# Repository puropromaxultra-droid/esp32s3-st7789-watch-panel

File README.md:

# 桌面电子屏 · ESP32-S3 + 手表拆机 ST7789

> 一块 3.5 元的智能手表拆机屏，一颗 ESP32-S3，四层自制 PCB（34×50mm），
> 手写驱动、无第三方库：七页可交互界面、GIF 动画专辑、WiFi 天气时钟、手机推流放音乐。
>
> *A pocket-sized ESP32-S3 info panel driving a salvaged smartwatch ST7789 (240×240):
> hand-written driver, GIF album, weather clock and phone-streamed music. It also has
> a battery, a speaker and a custom 4-layer PCB.*
>
> **状态**：V5 板已打样、焊接、在用（2026-11）。代码、PCB、Gerber、BOM、嘉立创工程源文件都在本仓库。
>
> **⚠️ 补丁 1（2026-11-25）** 装机后发现两个**只能改板**的问题：A 键接在 IO0（BOOT strapping 脚），
> 焊错就每次上电进下载模式；老王屏的排线不居中且必须朝下，导致装壳后屏偏，下一版要把屏换到元件面、
> 电池和扬声器补到背面原屏区。两处都在「二、硬件」里单独写了 ⚠️ 小节，改板前先看。

---

## 一、能干什么

七页界面，短按 A 键翻页：

| 页 | 内容 |
|---|---|
| **GIF** | 240×240 动画，从外挂 flash 读，**支持多条专辑**（长按 A/B 切换，右上角显示 `2/5`） |
| **CLOCK** | 大号数字时间 + 日期 + 顶部天气（长按 B 立即刷新天气） |
| **FORECAST** | 三天卡片：日期、天气图标、最高/最低温、天气文字（长按重试） |
| **SUN** | 日出/日落时间 + 太阳轨迹弧与当前位置 + **月相**（名称、月龄、亮度%） |
| **MUSIC** | 音乐播放页：曲名（自动 1 行/2 行/跑马灯）、进度、**长按 A/B 调音量**（存 NVS） |
| **BAT** | 电池图标 + 百分比大字、电压、温度、充电状态（ADC + CHRG 脚） |
| **SYS** | WiFi 信号强度/IP、堆与 PSRAM、芯片温度、SPI 频率、运行时长 —— 排障用 |

**音乐**：手机浏览器打开 `http://<板子IP>/`，选本地音频文件，**由手机 JS 解码 + 重采样**
成 31250Hz/16bit/立体声，POST 到板子，写进外挂 flash 的 4MB 环形缓冲，再喂 I2S。

**开机**：Win98 风格四色旗 + 跑马灯 + 多声部开机音（可从按键跳过）。

**按键**：只有两个键。A = 翻页，B = 第二功能；**A+B 同按 700ms 回时钟**（随时逃生）。
长按按页面分派：MUSIC 音量、CLOCK 刷天气、GIF 切专辑、其余回时钟。

---

## 二、硬件

### 器件

| 件 | 型号 | 说明 |
|---|---|---|
| 屏 | ST7789 240×240 IPS | 手表拆机模块，`FPC-T1D3BP-129`，24P / 0.5mm |
| 主控 | **ESP32-S3-MINI-1-N8**（8MB，立创 C2913206） | LGA 底焊，板载天线（不是 1U） |
| 外挂 flash | **GD25Q128 16MB（U5）** | 存 GIF 专辑 + 音乐环形缓冲 + 音频 |
| 功放 | **MAX98357A（U4，QFN）** | I2S 直入 D 类，配 1609 8Ω 0.5W 喇叭 |
| LDO | XC6220B331MR | 500mA，WiFi 峰值不塌 |
| 防倒灌 | AO3401（Q2） | D=BAT S=VSYS G=VBUS |
| 电池 | 602535 软包 500mAh（带保护板） | TP4056-42 **ESOP-8** 充电 |
| PCB | **34 × 50 mm，4 层 1.6mm** | 嘉立创 ¥50/5 片 |

### 引脚（V5 一体板，和外接面包板的编号不同！）

| 功能 | GPIO |
|---|---|
| LCD SCK / MOSI / CS / DC / RST / BL | **12 / 11 / 10 / 9 / 14 / 13** |
| I2S BCLK / LRC / DIN | **15 / 16 / 17** |
| 电池 ADC | 1 |
| 充电状态 CHRG | 2 |
| 按键 A / B | **0（飞线 J6.1）/ 5** |
| U5 flash（16MB，HSPI） | CS 21 / SCK 38 / MOSI 39 / MISO 40 |

#### ⚠️ A 键（补丁 1：这一版踩的坑，务必先读）

**为什么会长成这样**——四步错下来的，每一步都合理，合起来就废了：

1. **原设计**：A 键走 `SW1 → BTN_A 网络 → U1 的 pad 8`，也就是 **IO4**。
2. **实板翻车**：U1 是 LGA 底焊，IO4 那个焊盘虚焊，按键按下去信号根本出不了模组——
   表现为「键完全没反应」，不是接触不良那种时灵时不灵。底焊脚没法补焊，只能飞线绕开。
3. **飞线选错脚**：板上的 **J6 是 1×02 排针，pad1 = IO0、pad2 = GND**，看着天生就是个按键口，
   就把 A 键改到 IO0 上——**当时只确认了"这两根针空着"，没确认 IO0 上电时是什么状态**。
4. **接线再错一次**：SW1 是 4 脚轻触开关，**pad1/pad2 在板上直接接 GND，只有 pad3/pad4 是 BTN_A 信号**。
   飞线落在 pad1/pad2 上，等于把 IO0 焊死在 0V。

> 这些都能在工程文件里自己核（`hardware/LCD-board-V5_2026-11-08.epro2`）：
> `SW1: pad1/2→GND, pad3/4→BTN_A`；`U1: pad4→IO0, pad8→BTN_A(=IO4), pad9→IO5(=BTN_B)`；
> `J6: pad1→IO0, pad2→GND`；`J5: pad1→BAT, pad2→GND`（电池口，别搞混）。

**于是**：IO0 被拉低，芯片在上电那一刻判定"要烧录"，直接进 ROM 下载模式——屏黑、程序不跑，
但串口照样能烧录成功。这就是最坑的地方：**看起来像程序坏了，其实是脚被按住不放**。

问题的根在于 **IO0 不是普通 GPIO，它是 ESP32-S3 的 BOOT strapping 脚**：

| 现象 | 原因 |
|---|---|
| 插电屏全黑、程序不跑，但串口能烧录 | IO0 在上电/复位瞬间是**低**，进了 ROM 下载模式 |
| 松手也进不去系统，必须先拔线再插 | SW1 有一端误焊到 GND 侧，IO0 被**常拉低** |
| 烧录成功但按 RST 不重启 | 同上，复位时 IO0 仍为低 |

补焊/返修时只有一条正确接法：

- **飞线两端 = J6.1（IO0）↔ SW1 的 pad3 或 pad4**。这两个脚才是 BTN_A 信号脚；
  SW1 的 pad1/pad2 板上已经连死 GND，**不要碰**，碰了就是 IO0 常接地；
- ★ 判定方法：万用表蜂鸣档量 SW1 相邻两脚——**响的那一对是 GND**，另一对才是信号；
- 装壳后**上电、按 RST 时不要按着 A**，松手再上电（按下 = IO0 变低，同样进下载模式）；
- 验收：量 **IO0 ↔ GND**，松手必须回到 **≥3.0V**（芯片内部上拉），按下去才接近 0V。
  松手还是 0V 就是焊错或搭锡，别急着怀疑程序。

现场怎么验：串口发 **`b`** 打实时电平 —— `[btn] A=H B=H (H=松开 L=按下)`，
按一下 A 应变 `L`，松手立刻回 `H`。串口灯一直刷 `L` = IO0 被短路到地，先查焊点。
再用 **`e`** 核对计数（先发 `E` 清零，按 10 下，`down A` 应该是 10）；
`down` 偏少是电信号没进来（飞线/触点），`down` 对但 `short` 少是被双键同按吞了。

> **下一版必须把 A 键挪到非 strapping 的普通 GPIO**，否则这个坑会跟着外壳一起交付。
> B 键（IO5）没有这个问题。

#### ⚠️ 结构装配：屏排线不居中，而且只能朝下（补丁 1）

老王这块拆机屏（`FPC-T1D3BP-129`）有两个物理事实，直接否掉了"屏体居中"这个最直觉的排布方式：

1. **FPC 排线不在屏体正中**，出线口偏向一侧。屏体按外框居中装上去，**可视区就是偏的**，
   外壳的衬边一边宽一边窄，肉眼很明显。
2. **排线只能朝下出**。这块屏的 FPC 是单面翻折，朝上或朝侧都会折到屏体背面、塞不进后腔。

所以定位基准只能是 **「可视区中心」+「FPC 向下」**，不能拿屏体外框当基准。
偏置量逐块量，别套用别人的数值（同一批拆机屏都不完全一致）。

**V5 的排布是错的，改法是屏换面：**

| | V5（原设计） | 补丁 1（正确排布） |
|---|---|---|
| 屏 | B 面（背面），y≈10~39.5 | **F 面（元件面）** |
| 电池 + 扬声器 | 分散在 B 面剩余区域 | **占用 B 面原来屏占的那块** |
| 排线方向 | 朝上（J1 在板顶 Y 11.05，屏体压在排线下方） | **朝下**，自然出板边 |

屏换到元件面后，背面整块空出来正好给电池（602535）和喇叭，不用再抢角落。
**J1（FPC 座）必须跟着屏走**：V5 里它在 **X 17.00 / Y 11.05**（贴板顶，通道 x 11.2~22.8、y 8~15.5），
排线改朝下以后这个位置一定得挪，别照着 V5 的坐标抄。

**装配顺序别搞反，反了一定返工：**

1. 先定 FPC 出线方向 = **向下**；
2. 再按**可视区**居中定屏位（不是屏体外框）；
3. 最后才排电池和扬声器 —— 它们的形状受限最小，天然是让位的一方。

> 嘉立创 EDA 工程源文件：`hardware/LCD-board-V5_2026-11-08.epro2`（2026-11-08 定稿，含 PCB + 原理图）。
> 上面这套改法还没落到工程里，是**下一版要改的**；那份文件是改之前的状态，别直接打样。

### 最小验证接线（面包板 / FPC 转接板）

```
转接板排针                  →  ESP32-S3
1  (LED+)                   →  3V3
2  (LED-)                   →  GND
4  (VCC)                    →  3V3
5  (IOVCC)                  →  3V3
11 (RD)                     →  3V3      ← 串口模式选择，SPI 模式下也要拉高
23 (逻辑地)                 →  GND      ← ★ 必须接，只接 LED- 不够
9  (SCK)                    →  IO4
12 (SDA/MOSI)               →  IO5
8  (CS)                     →  IO6
10 (DC)                     →  IO7
7  (RST)                    →  IO8
6  (IM)                     →  IO9      ← ★ 必须为高电平，见下
```

> **这张表是「镜像」的。** 转接板座子的 pin1 方向与屏排线丝印相反，硬插会把
> 3V3 撞到屏的 GND 触点上（会发烫）。本项目没翻排线，而是把杜邦线按 `排针 n ↔ 屏触点 25-n`
> 映射改插到镜像位置。你若能自由选择方向，优先按物理正序插，别用这张镜像表。

---

## 三、踩过的坑（这个项目 90% 的时间都在这）

### 1. IM 脚必须为高电平 — 否则背光亮、屏全黑

ST7789 的 `IM0/IM1/IM2` 决定接口模式。**IM 为低时不是 4 线 SPI 模式，初始化指令完全不生效**，
症状是：背光正常亮、屏幕纯黑。

这条坑了整整一天，期间误判成「WiFi 库干扰」「固件太大」「杜邦线撑不住 20 MHz」，全是假象。
结论来自原厂开源工程 [`BA4IHS/GD32E230-LaoWang`](https://github.com/BA4IHS/GD32E230-LaoWang)，
其 `TFT_LCD_Init()` 第一行就是 `TFT_LCD_IM12(1);`。

```cpp
digitalWrite(PIN_IM, HIGH);   // 不能省，也不能拉低
```

### 2. 逐字节 `SPI.transfer()` 是性能灾难

`SPI.transfer(uint8_t)` 每次都要等上一字节发完，实测 **1.5–2 µs/字节**。
一帧 115200 字节 → **约 200ms，只有 5fps**。而且**提高 SPI 时钟完全没用**，
瓶颈在 CPU 调用开销，不在时钟。

换成 `SPI.writeBytes()` 批量（每批 16 行 = 7680 字节），整帧期间 CS 保持低、
`0x2C` 只发一次（窗口在全屏初始化时设好），立刻变成 **约 35ms/帧**。

| 方案 | 单帧 | 帧率 |
|---|---|---|
| 10 MHz + 逐字节 `transfer()` | ~200 ms | ~5 fps |
| 26 MHz + `writeBytes()` 批量 | ~35 ms | 跑满 GIF 的 16.7 fps |
| 80 MHz + 批量 + 双核流水线 | **15.1 ms** | 60+ fps（推屏上限） |

### 3. 逻辑地必须单独接

只接 `LED-` 时背光能亮，但屏的逻辑地悬空 → 全黑。转接板的 1/2/22 都是 GND，
至少要保证逻辑地有回路。

### 4. FPC 座插反 = 3V3 被拉塌，症状伪装成「屏黑 + USB 反复枚举」

反过来插会把 3V3 短到 GND。看上去像固件坏了、像 USB 线不好、像模组烧了，
**实际是座子方向错了**。先摸屏排线附近烫不烫，再查软件。

### 5. QFN 的 EP 锡厚会把芯片顶起来，十几脚一起虚焊

MAX98357A（U4）底部的散热焊盘上锡太多，芯片被顶高 0.1mm，**16 个脚全部没接触到焊盘**。
现象：一切正常，就是没声音。

修法：涂助焊剂，风枪 280~300°C 从底部吹 40~60s 让它自己回流坐下。
**没声先查 EP，不要先怀疑 I2S 时序。**

### 6. 采样率不是随便填的：MCLK/fs 必须是 128 / 256 / 384 / 512

一开始设 40000Hz，听到的是**沙沙声**——因为 PLL 拆不出整数分频。
31250Hz 能整除（MCLK 8MHz），于是本项目所有音频都锁在 31250Hz。
★ 别为了「好听」改成 44100，除非整条时钟链重新算。

### 7. flash 擦除会拖死播放，以及「对称去抖」是个陷阱

- 64KB 块擦是**原子操作 150ms**，而 8KB 读缓冲只够 131ms → 必须用 32KB（94ms），
  并且**只在刚 refill 完那一刻擦**，交给独立任务做。实测播放速率才从 51200 爬到 62958 B/s。
- 按键用对称去抖（`millis()-tRaw > 20`）**永远等不到**：氧化触点一次按动是 1~3ms 的脉冲串，
  每个断点都在刷新计时器。改成**计数式**：1ms 采样、连续 2 次 LOW 判按下、松手等 16ms。

---

## 四、目录

| 路径 | 说明 |
|---|---|
| **`weather_clock/`** | ★ **主程序**。多文件拆分：`weather_clock.ino`（UI/页面/按键）+ `tft.h`（驱动）+ `gif_store.h`（GIF 专辑）+ `u5flash.h`（16MB flash）+ `spk.h`（音效合成）+ `player.h`/`webstream.h`（推流播放）+ `www.h`（手机端网页）+ `audio.h`（WAV 播放） |
| **`hardware/`** | ★ **V5 四层 PCB**：KiCad 工程、Gerber、BOM、采购清单、`EDA-画板指南.md`（314KB 实战记录，§1~§40）。**`LCD-board-V5_2026-11-08.epro2`** = 嘉立创 EDA 工程源文件（PCB + 原理图，补丁 1 之前的状态） |
| `tools/album.py` | **GIF 专辑管理**：`list / add / rm / mv / order / migrate`，走串口 |
| `tools/screenshot.py` | **串口截图**：发 `Z` 导当前帧、`z` 重画 logo 后导出，存 PNG。调 UI 不用靠眼睛 |
| `tools/转换GIF.bat` | 把 GIF 拖上去 = 转码 + 上传 + 写索引（一条龙） |
| `tools/gif2bin.py` | GIF → 板端格式（缩放/抽帧/降色/RLE），单帧超限自动降色 |
| `tools/btn_diag.py` `vol_test.py` | 按键计数、音量台阶的自动化验证 |
| `lcd_fast/` `lcd_player/` | 早期驱动版本（可直接对比 `transfer()` 与 `writeBytes()` 的差异） |
| `bare_lcd_test/` | 最小验证：初始化 + 纯色 + 彩条，用来确认接线 |
| `gif_player*/` `*_probe/` `*_test/` | 排查过程留下的探针程序，保留作记录 |

---

## 五、编译与烧录

1. Arduino IDE + **esp32 core 4.0.x**
2. **必须有 `weather_clock/secrets.h`**（已 gitignore）：
   ```cpp
   #define WIFI_SSID "your-ssid"
   #define WIFI_PASS "your-pass"
   ```
   从 `secrets.h.example` 复制改名。
3. 板子选 **ESP32-S3 Dev Module**，下面两项**必须改**，否则屏黑或刷不进去：
   - **USB CDC On Boot: `Enabled`** ← 不开就看不到串口输出
   - **Partition Scheme: `Huge APP (3MB No OTA/1MB SPIFFS)`** ← 否则固件装不下
4. 串口 115200。正常启动会依次打印 WiFi、NTP、天气、U5、专辑索引、缓冲分配。

### 串口命令

| 键 | 作用 |
|---|---|
| `n` / `p` | 下一页 / 上一页 |
| `l` / `L` | 注入「长按 A / 长按 B」 |
| `H` | 注入「A+B 同按」 |
| `P` | 打印当前页 / 音量 / 推流状态 |
| `h` | 推流统计（`rd` 必须 ≈ **62500 B/s**） |
| `y` | 只灌 I2S 静音块，测纯时钟速率（应 ≈ 31499Hz） |
| `Z` / `z` | 导出当前帧 / 重画 logo 后导出（配合 `screenshot.py`） |
| `V` / `I` | 读 / 写专辑索引 |
| `e` / `E` | 按键计数 / 清零 |
| `U` / `A` | 上传 GIF / 音频 |

---

## 六、换 GIF、加音乐

**GIF**：把 `.gif` 拖到 `tools\转换GIF.bat` 上 → 自动转码 + 上传 + 写索引，屏上长按 A/B 切换。
或用命令行：

```bat
python tools\album.py add my.gif        :: 追加一条
python tools\album.py list              :: 看现有条目与占用
python tools\album.py rm 1              :: 删第 2 条（只改索引，数据等覆盖）
python tools\album.py mv 1 0            :: 调顺序
```

**音乐**：手机连同一 WiFi，浏览器开 `http://<屏上 SYS 页显示的 IP>/`，选文件即可播放。
网页里是 JS 解码 + 本地重采样到 31250Hz，**浏览器不给用的采样率会自动兜底**。

---

## 七、已知问题

- **A 键焊在 IO0 上（硬件缺陷）**：IO0 是 BOOT strapping 脚，IO0 被拉低时上电即进下载模式，
  软件无法规避。详见「二、硬件」的 A 键小节，下一版必须换脚。
- **屏装壳后不居中（结构缺陷）**：屏排线不在屏体正中，且只能朝下，V5 的屏位没考虑这一点。
  下一版屏换到元件面（F 面），电池和扬声器补到背面原屏区，详见「二、硬件」的装配小节。
- **天气接口只能走明文 HTTP**：`api.open-meteo.com` 的 ECDSA 证书会让 mbedTLS 握手失败，
  所以用了 HTTP/80 + 自计时 DNS。
- GIF 播放推到 8~17fps 取决于帧体积；单帧 >41KB 时转码脚本会自动降色。
- 外挂 flash 的 16MB 分了区：`0~2MB` 专辑、`2~6MB` 音乐环形、`8~16MB` 音频，
  其余留给将来。
- USB 供电不足时（满音量 + 满亮 + 推流），个别机器会欠压复位。

---

## 八、还有第二版

第二版是**重新设计的便携播放器**（TF 卡本地解码、侧装双喇叭、3.5mm 耳机、50×40 板），
不在本仓库，也不建议从本仓库改——音频架构完全不同。设计稿在另一个项目里，尚未开工。

---

## 致谢

- [`BA4IHS/GD32E230-LaoWang`](https://github.com/BA4IHS/GD32E230-LaoWang) — 原厂模块开源固件，
  IM 电平与完整初始化序列的结论出自这里
- ST7789 datasheet（写周期 16ns，SPI 上限约 62.5MHz）
- 立创 EDA / 嘉立创（打样）

## License

MIT，见 [LICENSE](LICENSE)。

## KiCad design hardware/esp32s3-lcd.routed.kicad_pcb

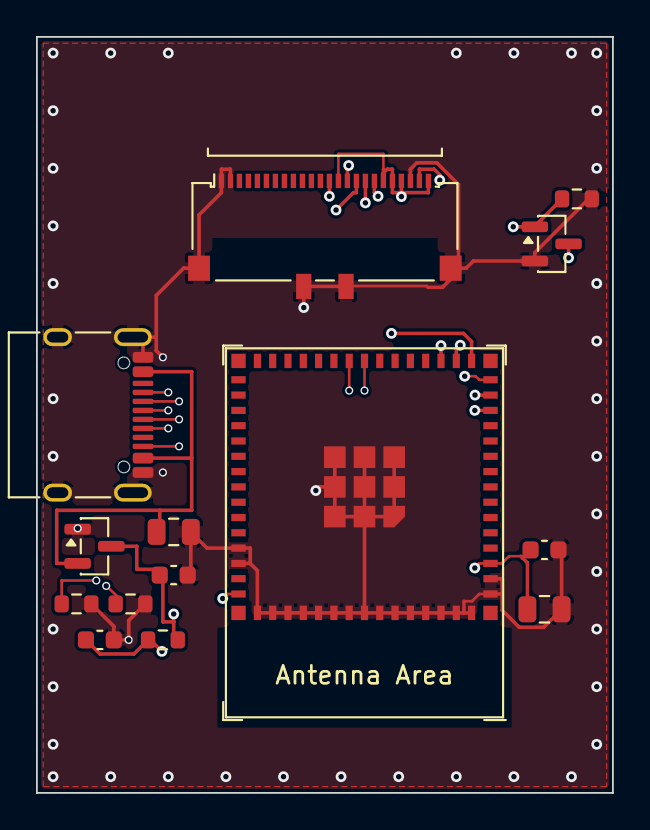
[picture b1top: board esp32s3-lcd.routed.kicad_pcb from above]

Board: 4 copper layers, 32.0 x 42.0 mm, 14 parts (0 on the bottom side), 15 nets.

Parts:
C1, C4: 10uF; C_0805_2012Metric
C2: 1uF; C_0603_1608Metric
C3, C5: 100nF; C_0603_1608Metric
J1: FPC 24P 0.5mm; Molex_502244-2430_1x24-1MP_P0.5mm_Horizontal
J2: USB-C 16P 单排; USB_C_Receptacle_XKB_U262-16XN-4BVC11
Q1: AO3400A; SOT-23
R1, R2: 5.1k; R_0603_1608Metric
R3: 10k; R_0603_1608Metric
R4: 100k; R_0603_1608Metric
U1: ESP32-S3-MINI-1-N8; ESP32-S3-MINI-1
U2: XC6206P332; SOT-23

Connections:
+3V3: C2.1, C3.1, C4.1, J1.14, J1.19, J1.20, J1.21, J1.24, R3.2, U1.3, U2.3
CC1: J2.A5, R1.1
CC2: J2.B5, R2.1
EN: C5.1, R3.1, U1.45
GND: C1.2, C2.2, C3.2, C4.2, C5.2, J1.1, J1.2, J1.22, J1.MP, J2.A1, J2.A12, J2.B1, J2.B12, J2.SH, Q1.2, R1.2, R2.2, R4.2, U1.1, U1.2, U1.42, U1.43, U1.46, U1.47, U1.48, U1.49, U1.50, U1.51, U1.52, U1.53, U1.54, U1.55, U1.56, U1.57, U1.58, U1.59, U1.60, U1.61, U2.1
LCD_BL: Q1.1, R4.1, U1.17
LCD_CS: J1.17, U1.14
LCD_DC: J1.15, U1.13
LCD_MOSI: J1.13, U1.15
LCD_RST: J1.18, U1.18
LCD_SCK: J1.16, U1.16
LED_K: J1.23, Q1.3
USB_DM: J2.A7, J2.B7, U1.23
USB_DP: J2.A6, J2.B6, U1.24
VBUS: C1.1, J2.A4, J2.A9, J2.B4, J2.B9, U2.2

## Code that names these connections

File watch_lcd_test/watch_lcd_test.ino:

/*
 * 手表拆机屏点亮测试（ESP32-S3 N16R8 + LovyanGFX）
 * ------------------------------------------------
 * 依赖：Arduino IDE 库管理器搜索 "LovyanGFX" 安装
 * 板型：ESP32S3 Dev Module（Flash 16MB，PSRAM 关闭即可，本例用不到）
 *
 * 接线（屏板 8 焊盘，顺序以板子丝印为准）：
 *   3V3  -> VCC（先试 3.3V；背光不亮再改接 5V）
 *   IO4  -> SCL   IO5  -> SDA
 *   IO6  -> DC    IO7  -> RES
 *   IO15 -> CS    IO16 -> BLK
 *   GND  -> GND
 *
 * 驱动 IC 未知。这种手表屏最常见的是 ST7789 / GC9A01 / GC9106，
 * 改下面 PANEL_XXX 宏逐个试；换宏后如仍黑屏，再把 spi_mode 改成 3、
 * invert 改成 false 再试。
 */

#define PANEL_ST7789
// #define PANEL_GC9A01
// #define PANEL_GC9106
// #define PANEL_ST7735
// #define PANEL_ILI9342

#define LCD_SCLK 4
#define LCD_MOSI 5
#define LCD_DC   6
#define LCD_RST  7
#define LCD_CS   15
#define LCD_BL   16

#include <LovyanGFX.hpp>

class WatchLCD : public lgfx::LGFX_Device {
  lgfx::Bus_SPI _bus;
#if defined(PANEL_ST7789)
  lgfx::Panel_ST7789 _panel;
#elif defined(PANEL_GC9A01)
  lgfx::Panel_GC9A01 _panel;
#elif defined(PANEL_GC9106)
  lgfx::Panel_GC9106 _panel;
#elif defined(PANEL_ST7735)
  lgfx::Panel_ST7735S _panel;
#else
  lgfx::Panel_ILI9342 _panel;
#endif

public:
  WatchLCD() {
    auto bc = _bus.config();
    bc.spi_host    = SPI2_HOST;    // FSPI
    bc.spi_mode    = 0;            // 黑屏可试 3
    bc.freq_write  = 40000000;     // 花屏就降到 20000000
    bc.freq_read   = 16000000;
    bc.spi_3wire   = true;
    bc.use_lock    = true;
    bc.dma_channel = 0;
    bc.pin_sclk    = LCD_SCLK;
    bc.pin_mosi    = LCD_MOSI;
    bc.pin_miso    = -1;
    bc.pin_dc      = LCD_DC;
    _bus.config(bc);
    setBus(&_bus);

    auto pc = _panel.config();
    pc.pin_cs          = LCD_CS;
    pc.pin_rst         = LCD_RST;
    pc.pin_busy        = -1;
    pc.panel_width     = 240;
    pc.panel_height    = 240;      // 若画面上下/左右错位，先调 offset_x/offset_y
    pc.memory_width    = 240;
    pc.memory_height   = 240;
    pc.invert          = true;     // IPS 屏常为 true；颜色反了改 false
    pc.rgb_order       = false;    // 红/蓝互换就改 true
    pc.dummy_read_pixel= 8;
    pc.dummy_read_bits = 1;
    pc.readable        = false;
    pc.offset_x        = 0;
    pc.offset_y        = 0;
    _panel.config(pc);
    setPanel(&_panel);
  }
};

WatchLCD lcd;

// 依次铺满几种颜色，方便判断显示是否正常
void colorCycle() {
  const uint16_t colors[] = { TFT_RED, TFT_GREEN, TFT_BLUE, TFT_WHITE, TFT_BLACK };
  const char* names[]    = { "RED", "GREEN", "BLUE", "WHITE", "BLACK" };
  for (int i = 0; i < 5; i++) {
    lcd.fillScreen(colors[i]);
    lcd.setTextDatum(textdatum_t::middle_center);
    lcd.setTextColor(colors[i] == TFT_BLACK ? TFT_WHITE : TFT_BLACK);
    lcd.drawString(names[i], 120, 120, &fonts::FreeSansBold12pt7b);
    delay(1500);
  }
}

void setup() {
  Serial.begin(115200);
  pinMode(LCD_BL, OUTPUT);
  digitalWrite(LCD_BL, HIGH);      // 个别屏背光是低电平有效，黑屏时试 LOW

  lcd.init();
  lcd.setRotation(0);
  lcd.fillScreen(TFT_BLACK);
  lcd.setTextDatum(textdatum_t::middle_center);
  lcd.setTextColor(TFT_GREEN, TFT_BLACK);
  lcd.drawString("Hello, watch LCD!", 120, 100, &fonts::FreeSansBold12pt7b);
  lcd.setTextColor(TFT_WHITE, TFT_BLACK);
  lcd.drawString("240x240 SPI test", 120, 140, &fonts::FreeSans12pt7b);
  Serial.println("LCD init done");
}

void loop() {
  colorCycle();
}
